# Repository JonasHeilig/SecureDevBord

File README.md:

# SecureDevBord
A DevBord Based on RP2040 with secure elements

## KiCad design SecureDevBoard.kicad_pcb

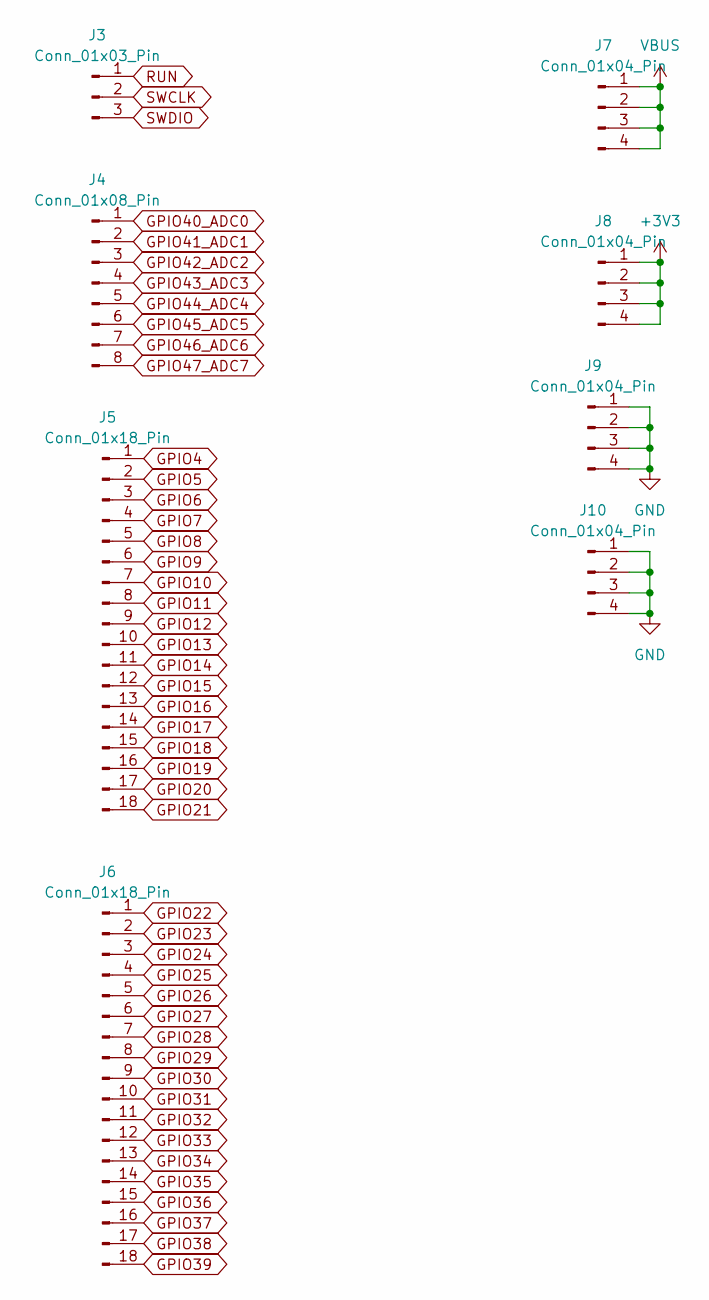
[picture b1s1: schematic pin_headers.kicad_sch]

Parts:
J3: Conn_01x03_Pin; PinSocket_1x03_P2.54mm_Vertical
J4: Conn_01x08_Pin; PinSocket_1x08_P2.54mm_Vertical
J5, J6: Conn_01x18_Pin; PinSocket_1x18_P2.54mm_Vertical
J7, J8, J9, J10: Conn_01x04_Pin; PinSocket_1x04_P2.54mm_Vertical

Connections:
+3V3: J8.1, J8.2, J8.3, J8.4; also elsewhere on the board
GND: J9.1, J9.2, J9.3, J9.4, J10.1, J10.2, J10.3, J10.4; also elsewhere on the board
GPIO4: J5.1; also elsewhere on the board
GPIO5: J5.2; also elsewhere on the board
GPIO6: J5.3; also elsewhere on the board
GPIO7: J5.4; also elsewhere on the board
GPIO8: J5.5; also elsewhere on the board
GPIO9: J5.6; also elsewhere on the board
GPIO10: J5.7; also elsewhere on the board
GPIO11: J5.8; also elsewhere on the board
GPIO12: J5.9; also elsewhere on the board
GPIO13: J5.10; also elsewhere on the board
GPIO14: J5.11; also elsewhere on the board
GPIO15: J5.12; also elsewhere on the board
GPIO16: J5.13; also elsewhere on the board
GPIO17: J5.14; also elsewhere on the board
GPIO18: J5.15; also elsewhere on the board
GPIO19: J5.16; also elsewhere on the board
GPIO20: J5.17; also elsewhere on the board
GPIO21: J5.18; also elsewhere on the board
GPIO22: J6.1; also elsewhere on the board
GPIO23: J6.2; also elsewhere on the board
GPIO24: J6.3; also elsewhere on the board
GPIO25: J6.4; also elsewhere on the board
GPIO26: J6.5; also elsewhere on the board
GPIO27: J6.6; also elsewhere on the board
GPIO28: J6.7; also elsewhere on the board
GPIO29: J6.8; also elsewhere on the board
GPIO30: J6.9; also elsewhere on the board
GPIO31: J6.10; also elsewhere on the board
GPIO32: J6.11; also elsewhere on the board
GPIO33: J6.12; also elsewhere on the board
GPIO34: J6.13; also elsewhere on the board
GPIO35: J6.14; also elsewhere on the board
GPIO36: J6.15; also elsewhere on the board
GPIO37: J6.16; also elsewhere on the board
GPIO38: J6.17; also elsewhere on the board
GPIO39: J6.18; also elsewhere on the board
GPIO40_ADC0: J4.1; also elsewhere on the board
GPIO41_ADC1: J4.2; also elsewhere on the board
GPIO42_ADC2: J4.3; also elsewhere on the board
GPIO43_ADC3: J4.4; also elsewhere on the board
GPIO44_ADC4: J4.5; also elsewhere on the board
GPIO45_ADC5: J4.6; also elsewhere on the board
GPIO46_ADC6: J4.7; also elsewhere on the board
GPIO47_ADC7: J4.8; also elsewhere on the board
RUN: J3.1; also elsewhere on the board
SWCLK: J3.2; also elsewhere on the board
SWDIO: J3.3; also elsewhere on the board
VBUS: J7.1, J7.2, J7.3, J7.4; also elsewhere on the board

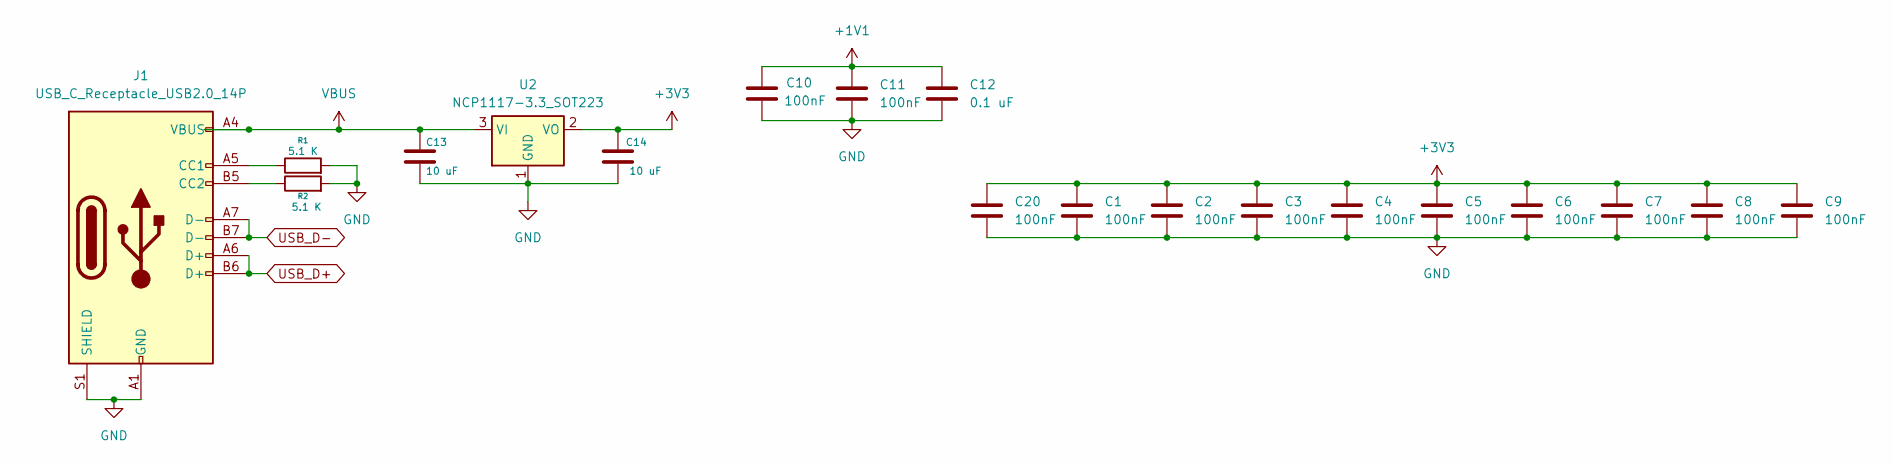
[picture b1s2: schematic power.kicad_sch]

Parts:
C1, C2, C3, C4, C5, C6, C7, C8, C9, C10, C11, C20: 100nF; C_0402_1005Metric
C12: 0.1 uF; C_0402_1005Metric
C13, C14: 10 uF; C_0402_1005Metric
J1: USB_C_Receptacle_USB2.0_14P; USB_C_Receptacle_HRO_TYPE-C-31-M-12
R1, R2: 5.1 K; R_0402_1005Metric
U2: NCP1117-3.3_SOT223; SOT-223-3_TabPin2

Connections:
+1V1: C10.1, C11.1, C12.1; also elsewhere on the board
+3V3: C1.1, C2.1, C3.1, C4.1, C5.1, C6.1, C7.1, C8.1, C9.1, C14.1, C20.1, U2.2 (VO); also elsewhere on the board
GND: C1.2, C2.2, C3.2, C4.2, C5.2, C6.2, C7.2, C8.2, C9.2, C10.2, C11.2, C12.2, C13.2, C14.2, C20.2, J1.A1 (GND), J1.A12 (GND), J1.B1 (GND), J1.B12 (GND), J1.S1 (SHIELD), R1.2, R2.2, U2.1 (GND); also elsewhere on the board
unnamed: J1.A5 (CC1), R1.1
unnamed: J1.B5 (CC2), R2.1
USB_D+: J1.A6 (D+), J1.B6 (D+); also elsewhere on the board
USB_D-: J1.A7 (D-), J1.B7 (D-); also elsewhere on the board
VBUS: C13.1, J1.A4 (VBUS), J1.A9 (VBUS), J1.B4 (VBUS), J1.B9 (VBUS), U2.3 (VI); also elsewhere on the board

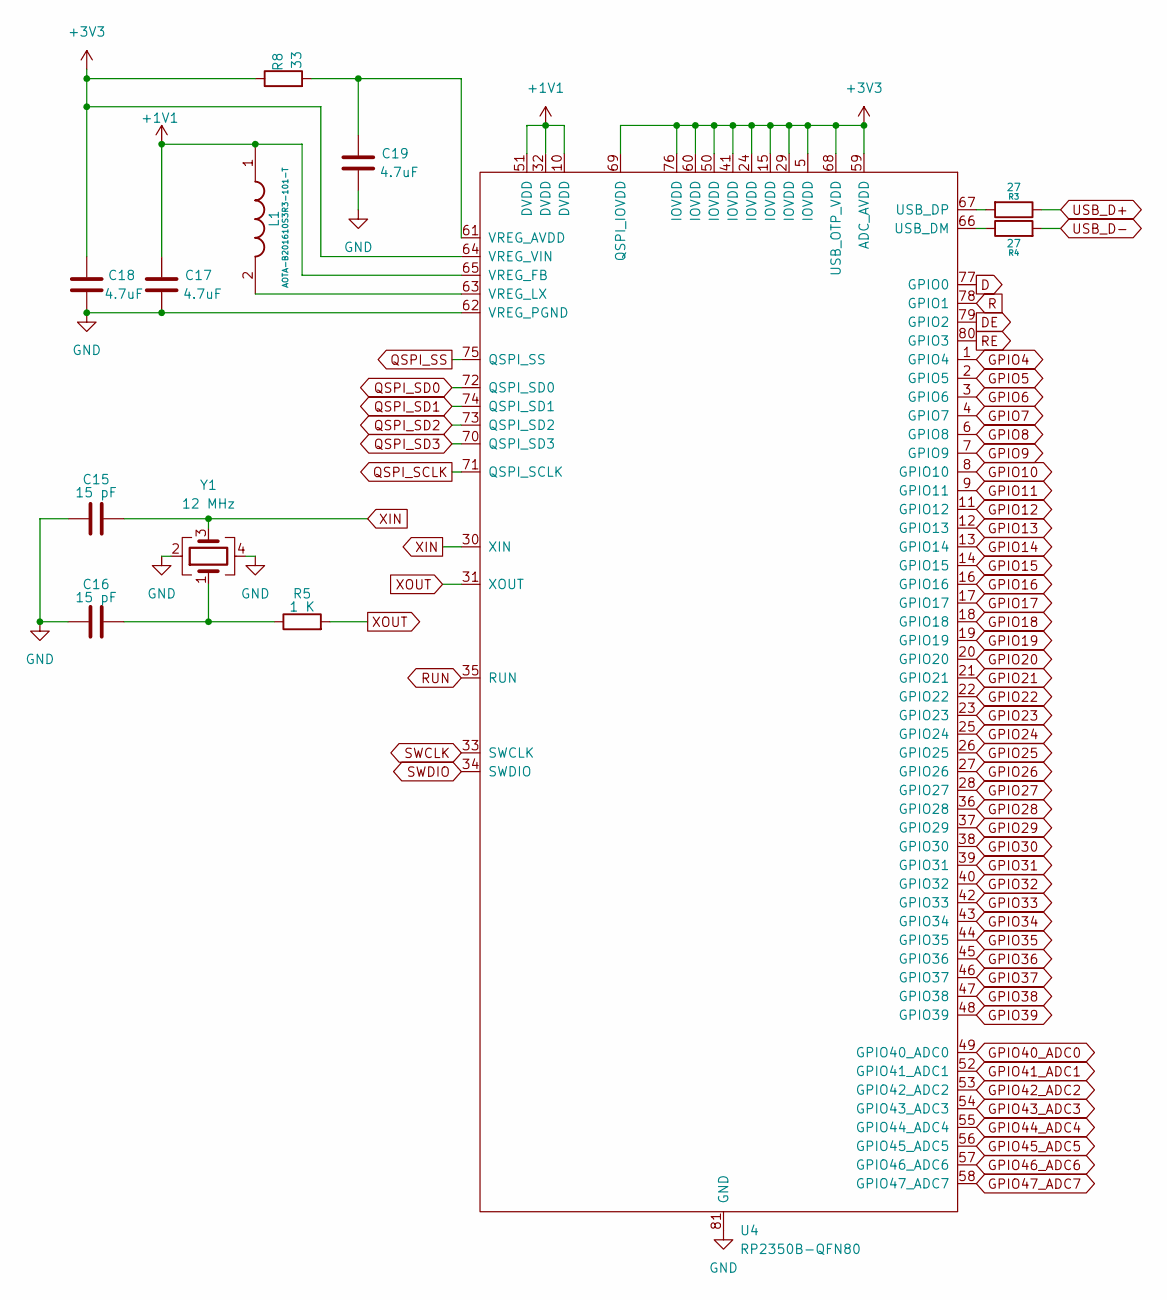
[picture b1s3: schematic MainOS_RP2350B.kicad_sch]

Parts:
C15, C16: 15 pF; C_0402_1005Metric
C17, C18, C19: 4.7uF; C_0402_1005Metric
L1: AOTA-B201610S3R3-101-T; AOTAB201610S3R3101T; Mouser Part Number 815-AB201610S3R3101T
R3, R4: 27; R_0402_1005Metric
R5: 1 K; R_0402_1005Metric
R8: 33; R_0402_1005Metric
U4: RP2350B-QFN80; QFN-80-1EP_10x10mm_P0.4mm_EP3.4x3.4mm
Y1: 12 MHz; Crystal_SMD_3225-4Pin_3.2x2.5mm

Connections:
+1V1: C17.1, L1.1, U4.10 (DVDD), U4.32 (DVDD), U4.51 (DVDD), U4.65 (VREG_FB); also elsewhere on the board
+3V3: C18.1, R8.1, U4.5 (IOVDD), U4.15 (IOVDD), U4.24 (IOVDD), U4.29 (IOVDD), U4.41 (IOVDD), U4.50 (IOVDD), U4.59 (ADC_AVDD), U4.60 (IOVDD), U4.64 (VREG_VIN), U4.68 (USB_OTP_VDD), U4.69 (QSPI_IOVDD), U4.76 (IOVDD); also elsewhere on the board
D: U4.77 (GPIO0); also elsewhere on the board
DE: U4.79 (GPIO2); also elsewhere on the board
GND: C15.1, C16.1, C17.2, C18.2, C19.2, U4.62 (VREG_PGND), U4.81 (GND), Y1.2, Y1.4; also elsewhere on the board
GPIO4: U4.1 (GPIO4); also elsewhere on the board
GPIO5: U4.2 (GPIO5); also elsewhere on the board
GPIO6: U4.3 (GPIO6); also elsewhere on the board
GPIO7: U4.4 (GPIO7); also elsewhere on the board
GPIO8: U4.6 (GPIO8); also elsewhere on the board
GPIO9: U4.7 (GPIO9); also elsewhere on the board
GPIO10: U4.8 (GPIO10); also elsewhere on the board
GPIO11: U4.9 (GPIO11); also elsewhere on the board
GPIO12: U4.11 (GPIO12); also elsewhere on the board
GPIO13: U4.12 (GPIO13); also elsewhere on the board
GPIO14: U4.13 (GPIO14); also elsewhere on the board
GPIO15: U4.14 (GPIO15); also elsewhere on the board
GPIO16: U4.16 (GPIO16); also elsewhere on the board
GPIO17: U4.17 (GPIO17); also elsewhere on the board
GPIO18: U4.18 (GPIO18); also elsewhere on the board
GPIO19: U4.19 (GPIO19); also elsewhere on the board
GPIO20: U4.20 (GPIO20); also elsewhere on the board
GPIO21: U4.21 (GPIO21); also elsewhere on the board
GPIO22: U4.22 (GPIO22); also elsewhere on the board
GPIO23: U4.23 (GPIO23); also elsewhere on the board
GPIO24: U4.25 (GPIO24); also elsewhere on the board
GPIO25: U4.26 (GPIO25); also elsewhere on the board
GPIO26: U4.27 (GPIO26); also elsewhere on the board
GPIO27: U4.28 (GPIO27); also elsewhere on the board
GPIO28: U4.36 (GPIO28); also elsewhere on the board
GPIO29: U4.37 (GPIO29); also elsewhere on the board
GPIO30: U4.38 (GPIO30); also elsewhere on the board
GPIO31: U4.39 (GPIO31); also elsewhere on the board
GPIO32: U4.40 (GPIO32); also elsewhere on the board
GPIO33: U4.42 (GPIO33); also elsewhere on the board
GPIO34: U4.43 (GPIO34); also elsewhere on the board
GPIO35: U4.44 (GPIO35); also elsewhere on the board
GPIO36: U4.45 (GPIO36); also elsewhere on the board
GPIO37: U4.46 (GPIO37); also elsewhere on the board
GPIO38: U4.47 (GPIO38); also elsewhere on the board
GPIO39: U4.48 (GPIO39); also elsewhere on the board
GPIO40_ADC0: U4.49 (GPIO40_ADC0); also elsewhere on the board
GPIO41_ADC1: U4.52 (GPIO41_ADC1); also elsewhere on the board
GPIO42_ADC2: U4.53 (GPIO42_ADC2); also elsewhere on the board
GPIO43_ADC3: U4.54 (GPIO43_ADC3); also elsewhere on the board
GPIO44_ADC4: U4.55 (GPIO44_ADC4); also elsewhere on the board
GPIO45_ADC5: U4.56 (GPIO45_ADC5); also elsewhere on the board
GPIO46_ADC6: U4.57 (GPIO46_ADC6); also elsewhere on the board
GPIO47_ADC7: U4.58 (GPIO47_ADC7); also elsewhere on the board
unnamed: C16.2, R5.1, Y1.1
unnamed: R4.1, U4.66 (USB_DM)
unnamed: R3.2, U4.67 (USB_DP)
unnamed: C19.1, R8.2, U4.61 (VREG_AVDD)
unnamed: L1.2, U4.63 (VREG_LX)
QSPI_SCLK: U4.71 (QSPI_SCLK); also elsewhere on the board
QSPI_SD0: U4.72 (QSPI_SD0); also elsewhere on the board
QSPI_SD1: U4.74 (QSPI_SD1); also elsewhere on the board
QSPI_SD2: U4.73 (QSPI_SD2); also elsewhere on the board
QSPI_SD3: U4.70 (QSPI_SD3); also elsewhere on the board
QSPI_SS: U4.75 (QSPI_SS); also elsewhere on the board
R: U4.78 (GPIO1); also elsewhere on the board
RE: U4.80 (GPIO3); also elsewhere on the board
RUN: U4.35 (RUN); also elsewhere on the board
SWCLK: U4.33 (SWCLK); also elsewhere on the board
SWDIO: U4.34 (SWDIO); also elsewhere on the board
USB_D+: R3.1; also elsewhere on the board
USB_D-: R4.2; also elsewhere on the board
XIN: C15.2, U4.30 (XIN), Y1.3
XOUT: R5.2, U4.31 (XOUT)

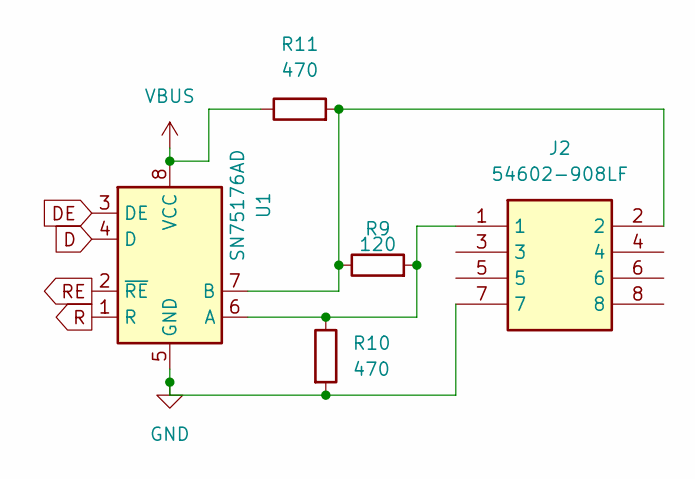
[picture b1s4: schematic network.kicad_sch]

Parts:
J2: 54602-908LF; 54602908LF; Manufacturer_Part_Number 54602-908LF
R9: 120; R_0402_1005Metric
R10, R11: 470; R_0402_1005Metric
U1: SN75176AD; SOIC-8_3.9x4.9mm_P1.27mm

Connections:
D: U1.4 (D); also elsewhere on the board
DE: U1.3 (DE); also elsewhere on the board
GND: J2.7, R10.2, U1.5 (GND); also elsewhere on the board
unnamed: J2.1, R9.2, R10.1, U1.6 (A)
unnamed: J2.2, R9.1, R11.2, U1.7 (B)
R: U1.1 (R); also elsewhere on the board
RE: U1.2 (~RE); also elsewhere on the board
VBUS: R11.1, U1.8 (VCC); also elsewhere on the board

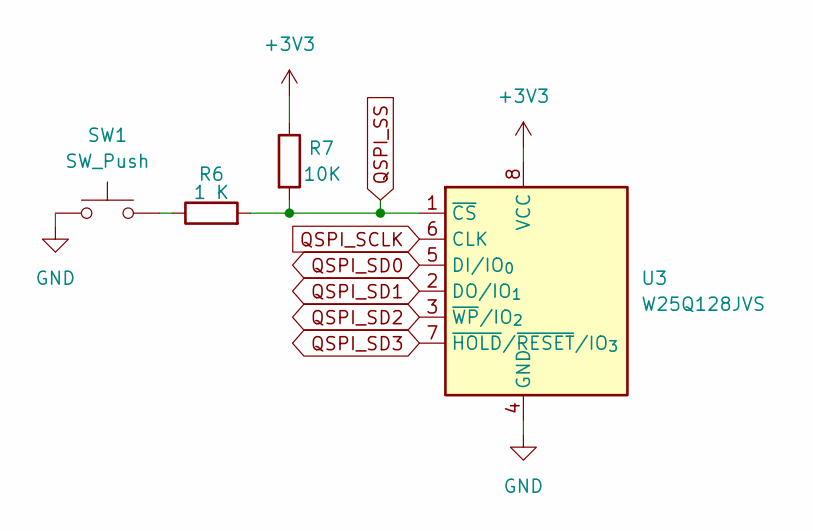
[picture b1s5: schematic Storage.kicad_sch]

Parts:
R6: 1 K; R_0402_1005Metric
R7: 10K; R_0402_1005Metric
SW1: SW_Push; smd_switch_sunrom4388
U3: W25Q128JVS; SOIC-8_5.3x5.3mm_P1.27mm

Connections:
+3V3: R7.1, U3.8 (VCC); also elsewhere on the board
GND: SW1.1, U3.4 (GND); also elsewhere on the board
unnamed: R6.1, SW1.2
QSPI_SCLK: U3.6 (CLK); also elsewhere on the board
QSPI_SD0: U3.5 (DI/IO_{0}); also elsewhere on the board
QSPI_SD1: U3.2 (DO/IO_{1}); also elsewhere on the board
QSPI_SD2: U3.3 (~WP/IO_{2}); also elsewhere on the board
QSPI_SD3: U3.7 (~HOLD/~RESET/IO_{3}); also elsewhere on the board
QSPI_SS: R6.2, R7.2, U3.1 (~CS); also elsewhere on the board

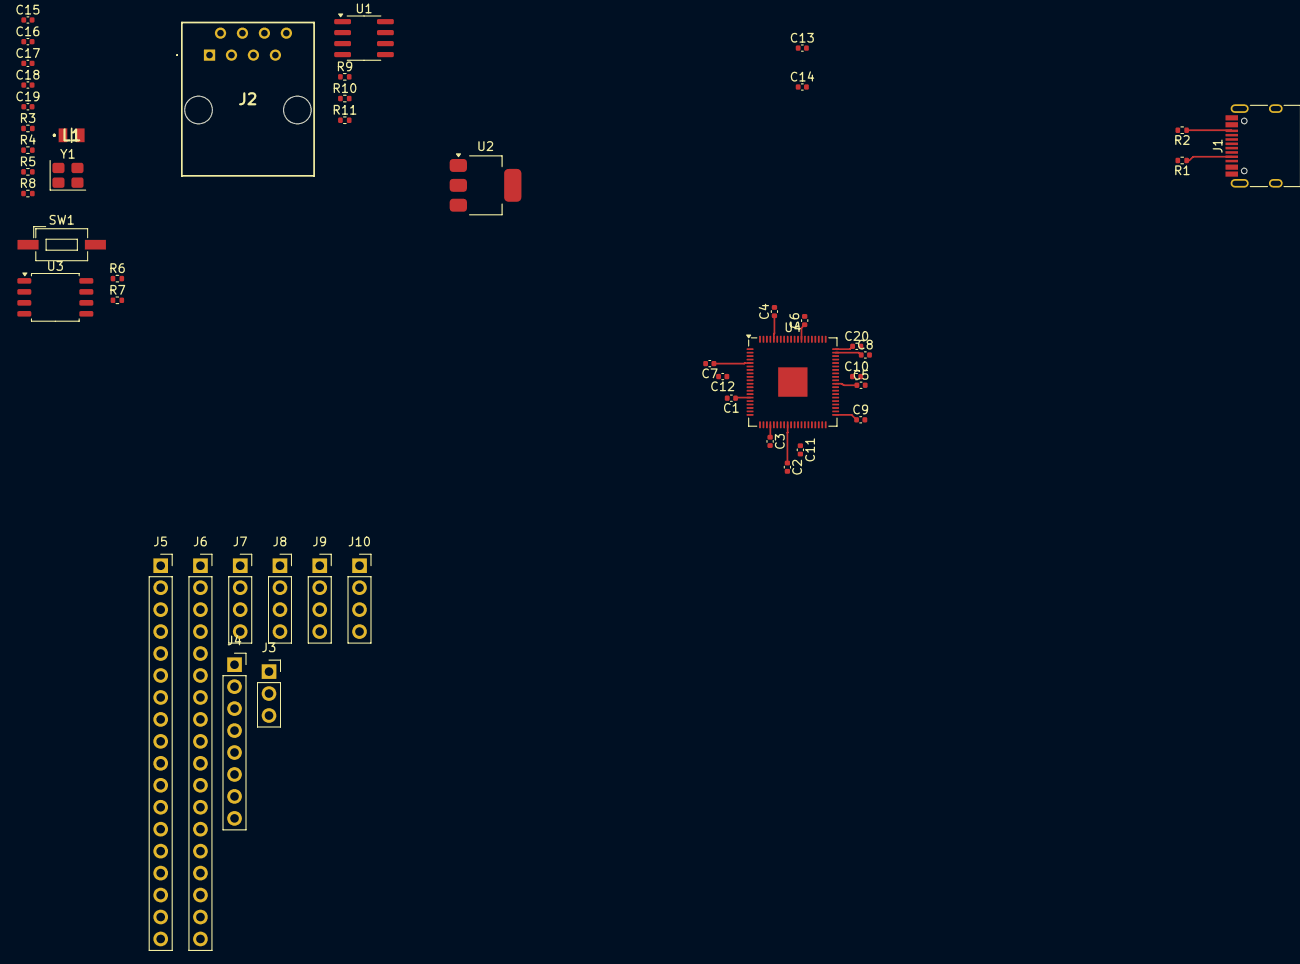
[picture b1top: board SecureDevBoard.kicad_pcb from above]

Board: 2 copper layers, 48 parts (0 on the bottom side), 75 nets.

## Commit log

2025-10-21 Add Basic Parts of the DevBord from the Blueprints Guides Page
2025-10-21 remove ._.* files
2025-10-21 edit gitignore
2025-10-23 Journal2-Migrate RP2040 to RP2350b
2025-10-24 Start to make a modular bus system for a modular comunication
2025-10-25 Restore
2025-10-25 Restore Local Backup
